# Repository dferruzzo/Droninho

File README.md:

# Droninho

Este repositório apresenta um diagrama eletrônico esquemático feito em [KiCad 9.0](https://www.kicad.org/) de um drone pequeno baseado em ESP32. 

---

## Objetivo

- Produzir a placa de circuito impresso do hardware do droninho.

---

## To-Do

- [x] ERC OKAY!
- [x] Criar PCB.
- [x] Checar footprint do conectores *J2, J3, J4, J5*.
- [x] Checar footprint do conector da bateria *J1*.
- [x] Checar PCB rules. Corrigir footprint do MPU9250.
- [x] Add connector for I2C and Power to connect other components for testing
- [x] Consider connection for RC receiver (cancelled!).
- [x] O MPU9250 está muito perto do ESP32 na placa.
- [x] Adicionar layer com nomes dos componentes e conectores. 
- [x] For review.
- [x] Duvida: A distancia entre a entrada USB do ESP32 e o MPU9250 é suficiente? Não.
- [x] Mudar de lado o ESP32 OK.
- [x] Mudar footprint dos diodos e resistências OK.
- [x] Colocar uma fonte regulada de 3.3v. https://docs.espressif.com/projects/esp-dev-kits/en/latest/esp32/esp32-devkitc/user_guide.html#power-supply-options https://dl.espressif.com/dl/schematics/esp32_devkitc_v4_sch.pdf
- [x] Mudar os footprints dos conectores dos motores e da bateria (só da bateria).
- [ ] Mandar a produzir com PCBway.

---
 
## Esquemático

[Diagrama elétrico esquemático.](schematics.pdf)

---

## PCB

PCB Front

PCB Back

---

## 3D model

---

## Como Contribuir

1. Faça um fork deste repositório.
2. Crie uma branch para sua feature (`git checkout -b feature/nome-da-feature`).
3. Faça commit das suas alterações (`git commit -m 'Adiciona nova feature'`).
4. Faça push para a branch (`git push origin feature/nome-da-feature`).
5. Abra um Pull Request.

---

## Licença

Este projeto está licenciado sob a licença MIT.

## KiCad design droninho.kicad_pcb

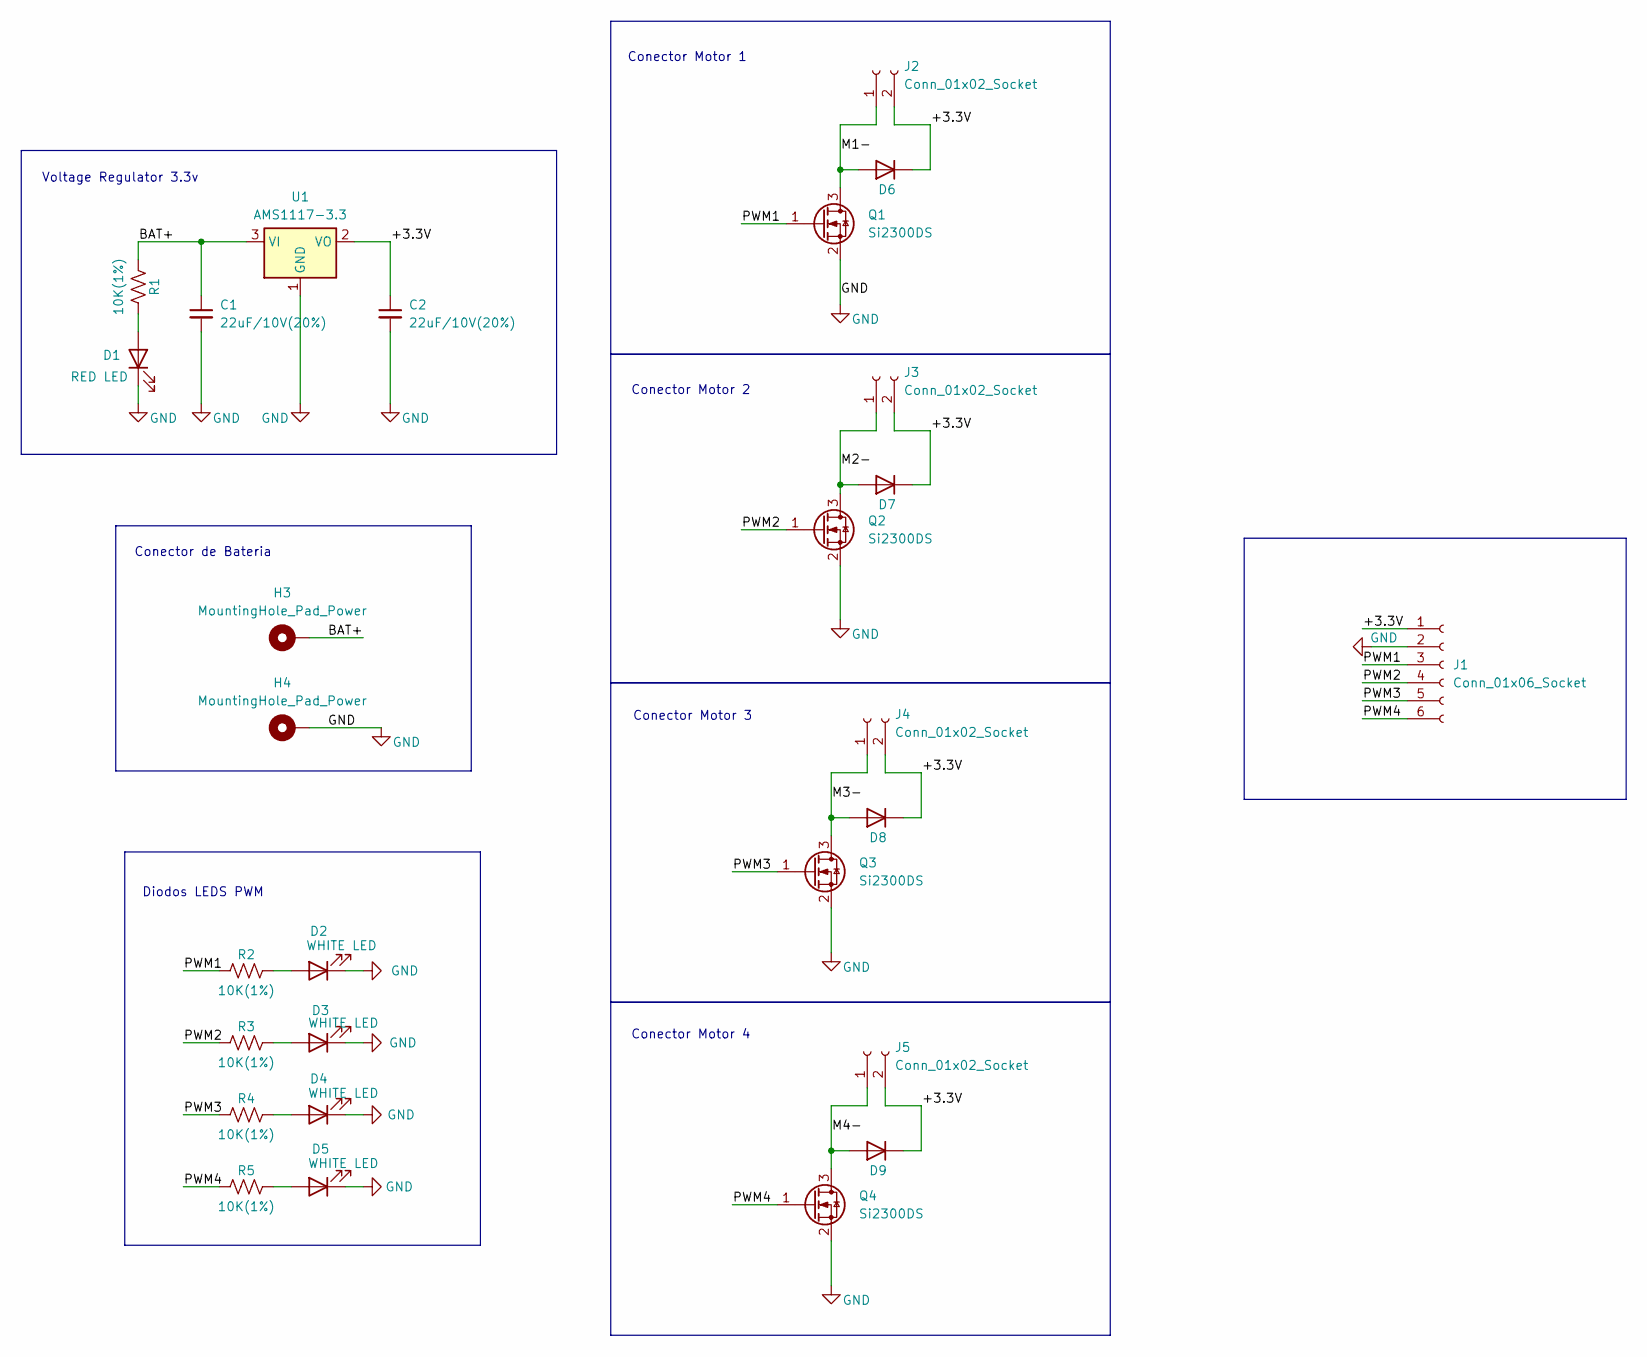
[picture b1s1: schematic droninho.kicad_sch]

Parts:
C1, C2: 22uF/10V(20%); C_0805_2012Metric_Pad1.18x1.45mm_HandSolder; Mfg Part # GRM21BR61A226ME51L
D1: RED LED; LED_0805_2012Metric_Pad1.15x1.40mm_HandSolder; Mfg Part # 150080RS75000
D2, D3, D4, D5: WHITE LED; LED_0805_2012Metric_Pad1.15x1.40mm_HandSolder; Mfg Part # HSMW-C170
D6, D7, D8, D9: 1N4148W SOD-123 SMD 100V 2A (A2); D_SOD-123; Mfg Part # 1N4148W
H3, H4: MountingHole_Pad_Power; MountingHole_2.2mm_M2_Pad_TopBottom
J1: Conn_01x06_Socket; JST_PH_B6B-PH-K_1x06_P2.00mm_Vertical; Mfg Part # BM06B-PASS-TF(LF)(SN)
J2, J3, J4, J5: Conn_01x02_Socket; JST_PH_B2B-PH-K_1x02_P2.00mm_Vertical; Mfg Part # BM02B-PASS-TF(LF)(SN)
Q1, Q2, Q3, Q4: Si2300DS; SOT-23; Mfg Part # SI2300DS-T1-BE3
R1, R2, R3, R4, R5: 10K(1%); R_0805_2012Metric_Pad1.20x1.40mm_HandSolder; Mfg Part # ERJ-6ENF1002V
U1: AMS1117-3.3; SOT-223-3_TabPin2; Mfg Part # LM1117MPX-3.3/NOPB

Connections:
/+3.3V: C2.1, D6.1 (K), D7.1 (K), D8.1 (K), D9.1 (K), J1.1, J2.2, J3.2, J4.2, J5.2, U1.2 (VO)
/BAT+: C1.1, H3.1, R1.1, U1.3 (VI)
/M1-: D6.2 (A), J2.1, Q1.3 (D)
/M2-: D7.2 (A), J3.1, Q2.3 (D)
/M3-: D8.2 (A), J4.1, Q3.3 (D)
/M4-: D9.2 (A), J5.1, Q4.3 (D)
/PWM1: J1.3, Q1.1 (G), R2.1
/PWM2: J1.4, Q2.1 (G), R3.1
/PWM3: J1.5, Q3.1 (G), R4.1
/PWM4: J1.6, Q4.1 (G), R5.1
GND: C1.2, C2.2, D1.1 (K), D2.1 (K), D3.1 (K), D4.1 (K), D5.1 (K), H4.1, J1.2, Q1.2 (S), Q2.2 (S), Q3.2 (S), Q4.2 (S), U1.1 (GND)
unnamed: D1.2 (A), R1.2
unnamed: D2.2 (A), R2.2
unnamed: D3.2 (A), R3.2
unnamed: D4.2 (A), R4.2
unnamed: D5.2 (A), R5.2

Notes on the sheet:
Conector Motor 3
Conector Motor 4
Diodos LEDS PWM
Conector de Bateria
Conector Motor 2
Conector Motor 1
Voltage Regulator 3.3v

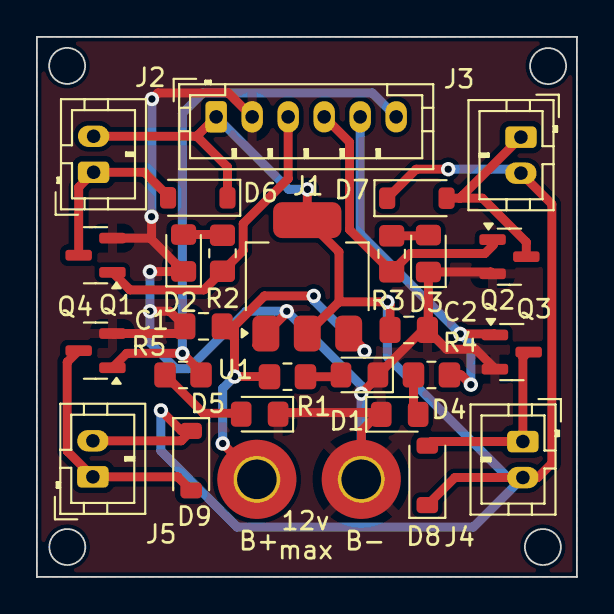
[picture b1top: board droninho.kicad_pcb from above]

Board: 2 copper layers, 30.0 x 30.0 mm, 28 parts (0 on the bottom side), 16 nets.

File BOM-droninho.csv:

"Id";"Designador";"Footprint";"Quantidade";"Designação";"Fornecedor e referência";
1;"R2,R1,R4,R3";"R_0805_2012Metric_Pad1.20x1.40mm_HandSolder";4;"10K";;;
2;"Q1,Q4,Q2,Q3";"SOT-23";4;"SI2300";;;
3;"J5";"JST_PH_B2B-PH-K_1x02_P2.00mm_Vertical";1;"M4";;;
4;"J7";"PinHeader_1x04_P2.54mm_Vertical";1;"TXD0/RXD0";;;
5;"J8,J6";"PinHeader_1x04_P2.54mm_Vertical";2;"I2C";;;
6;"J2";"JST_PH_B2B-PH-K_1x02_P2.00mm_Vertical";1;"M2";;;
7;"D4,D3,D2,D1";"D_SOD-110";4;"1N4148";;;
8;"J3";"JST_PH_B2B-PH-K_1x02_P2.00mm_Vertical";1;"M1";;;
9;"U1";"ESP32_30pin vertical WIFI";1;"ESP32 Dev Kit";;;
10;"J4";"JST_PH_B2B-PH-K_1x02_P2.00mm_Vertical";1;"M3";;;
11;"U4";"MPU-9250-6500";1;"MPU9250/6500";;;
12;"J1";"JST_EH_B2B-EH-A_1x02_P2.50mm_Vertical";1;"Conn_01x02_Pin";;;

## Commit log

2025-03-16 Electrical part finished
2025-03-16 Readme added
2025-03-16 add nets to schematic
2025-03-16 ERC OK!
2025-03-18 ERC Done
2025-03-18 ERC marked as done
2025-03-19 PCB feito.
2025-03-19 readme updated.
2025-03-19 README.md fixed.
2025-03-19 Footprints checked.
2025-03-21 PCB finalizado.
2025-03-21 3dmodel updated.
2025-03-21 To-Do updated
2025-03-21 readme updated
2025-03-22 Ready for review.
2025-03-22 small changes
2025-03-22 PDF PCB-front and PCB-back added.
2025-03-23 Versão com WIFI de fora da placa.
2025-03-23 Readme corrected.
2025-03-23 BOM, DCR e erc OKAY.
2025-03-25 Correções em footprints e troca de lado do ESP32.
2025-03-26 voltage regulator added
2025-03-27 ERC done!
2025-03-27 Source and Battery connector added!
2025-04-03 pull-down resistors removed, change leds positions.
2025-04-03 Ajustes finais no PCB
2025-04-04 packages updated
2025-04-04 Cleaning up.
2025-04-07 add manufacturer and part number for BOM.
2025-04-08 BOM updated.
2025-04-12 cleaning up old files
2025-04-12 driver PCB ready
2025-04-12 small updates
2025-04-17 driver finalizado.
2025-06-06 gerber files added
2026-05-22 AMS1117 datasheet added.
